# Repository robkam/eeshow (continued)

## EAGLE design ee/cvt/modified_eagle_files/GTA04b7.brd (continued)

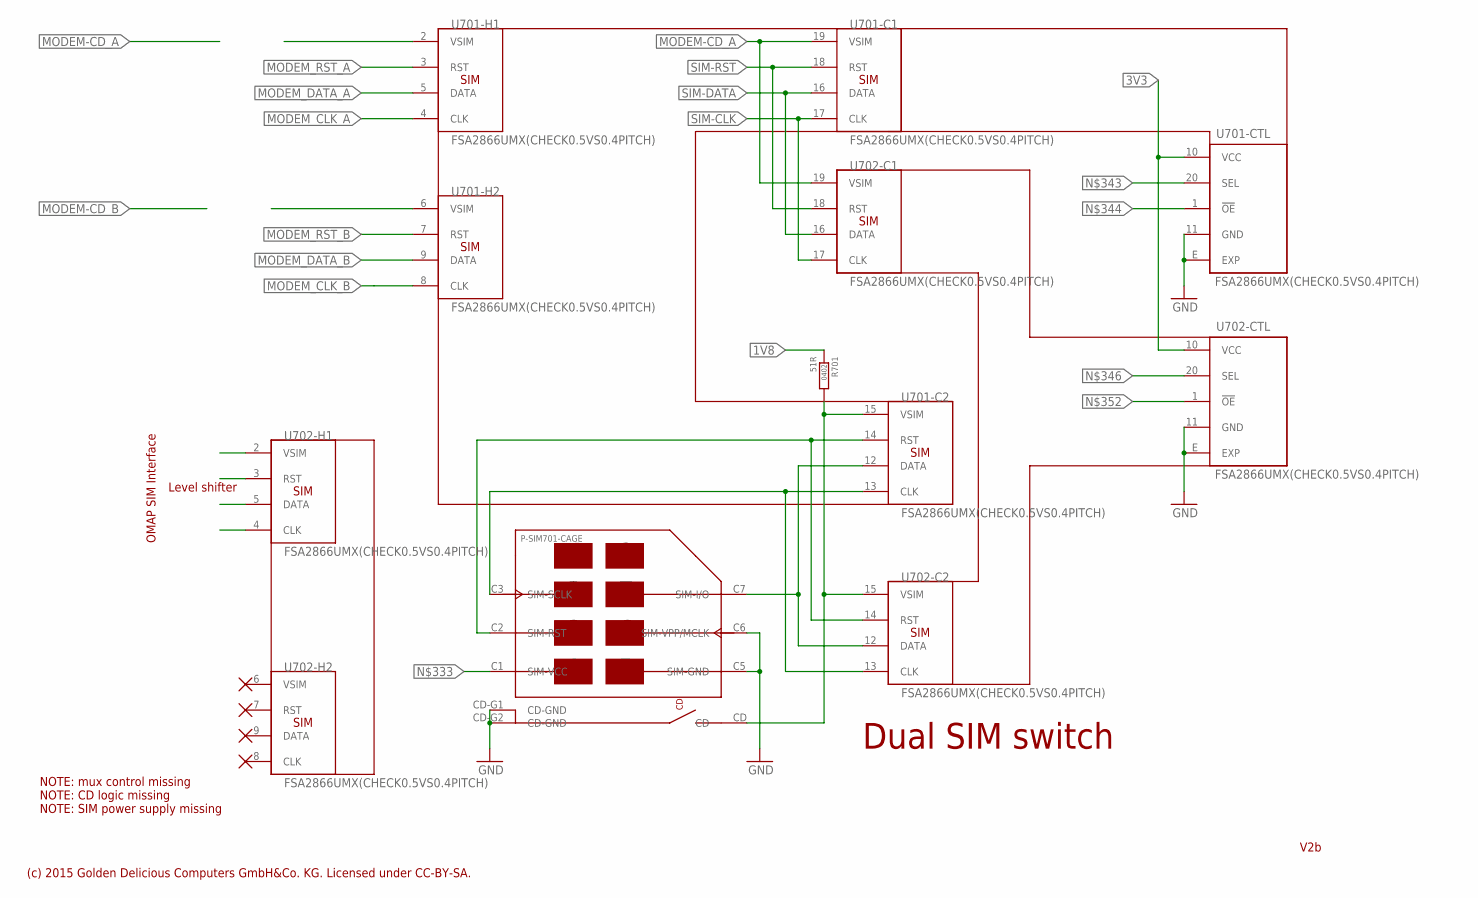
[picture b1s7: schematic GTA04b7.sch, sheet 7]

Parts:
P-SIM701: SIM-SLOT-6PIN+CD-CHECK-PINS; SJ106220
R701: 51R; SMD-0402
U701, U702: FSA2866UMX(CHECK0.5VS0.4PITCH); S-PWQFN-N20-0.5

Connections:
1V8: R701.1; also elsewhere on the board
3V3: U701.10 (VCC), U702.10 (VCC); also elsewhere on the board
GND: P-SIM701.C5 (SIM-GND), P-SIM701.C6 (SIM-VPP/MCLK), P-SIM701.CD-G1 (CD-GND), P-SIM701.CD-G2 (CD-GND), U701.11 (GND), U701.E (EXP), U702.11 (GND), U702.E (EXP); also elsewhere on the board
MODEM-CD_A: U701.19 (VSIM), U702.19 (VSIM); also elsewhere on the board
MODEM_CLK_A: U701.4 (CLK); also elsewhere on the board
MODEM_CLK_B: U701.8 (CLK)
MODEM_DATA_A: U701.5 (DATA); also elsewhere on the board
MODEM_DATA_B: U701.9 (DATA)
MODEM_RST_A: U701.3 (RST); also elsewhere on the board
MODEM_RST_B: U701.7 (RST)
unnamed: P-SIM701.C3 (SIM-SCLK), U701.13 (CLK), U702.13 (CLK)
unnamed: P-SIM701.C2 (SIM-RST), U701.14 (RST), U702.14 (RST)
unnamed: P-SIM701.CD, R701.2, U701.15 (VSIM), U702.15 (VSIM)
unnamed: P-SIM701.C7 (SIM-I/O), U701.12 (DATA), U702.12 (DATA)
SHIELD: P-SIM701.S1 (SHIELD), P-SIM701.S2 (SHIELD); also elsewhere on the board
SIM-CLK: U701.17 (CLK), U702.17 (CLK); also elsewhere on the board
SIM-DATA: U701.16 (DATA), U702.16 (DATA); also elsewhere on the board
SIM-RST: U701.18 (RST), U702.18 (RST); also elsewhere on the board
VSIM: U702.6 (VSIM)

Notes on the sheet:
Dual SIM switch
(c) 2015 Golden Delicious Computers GmbH&Co. KG. Licensed under CC-BY-SA.
V2b
Level shifter
OMAP SIM Interface
NOTE: mux control missing NOTE: CD logic missing NOTE: SIM power supply missing

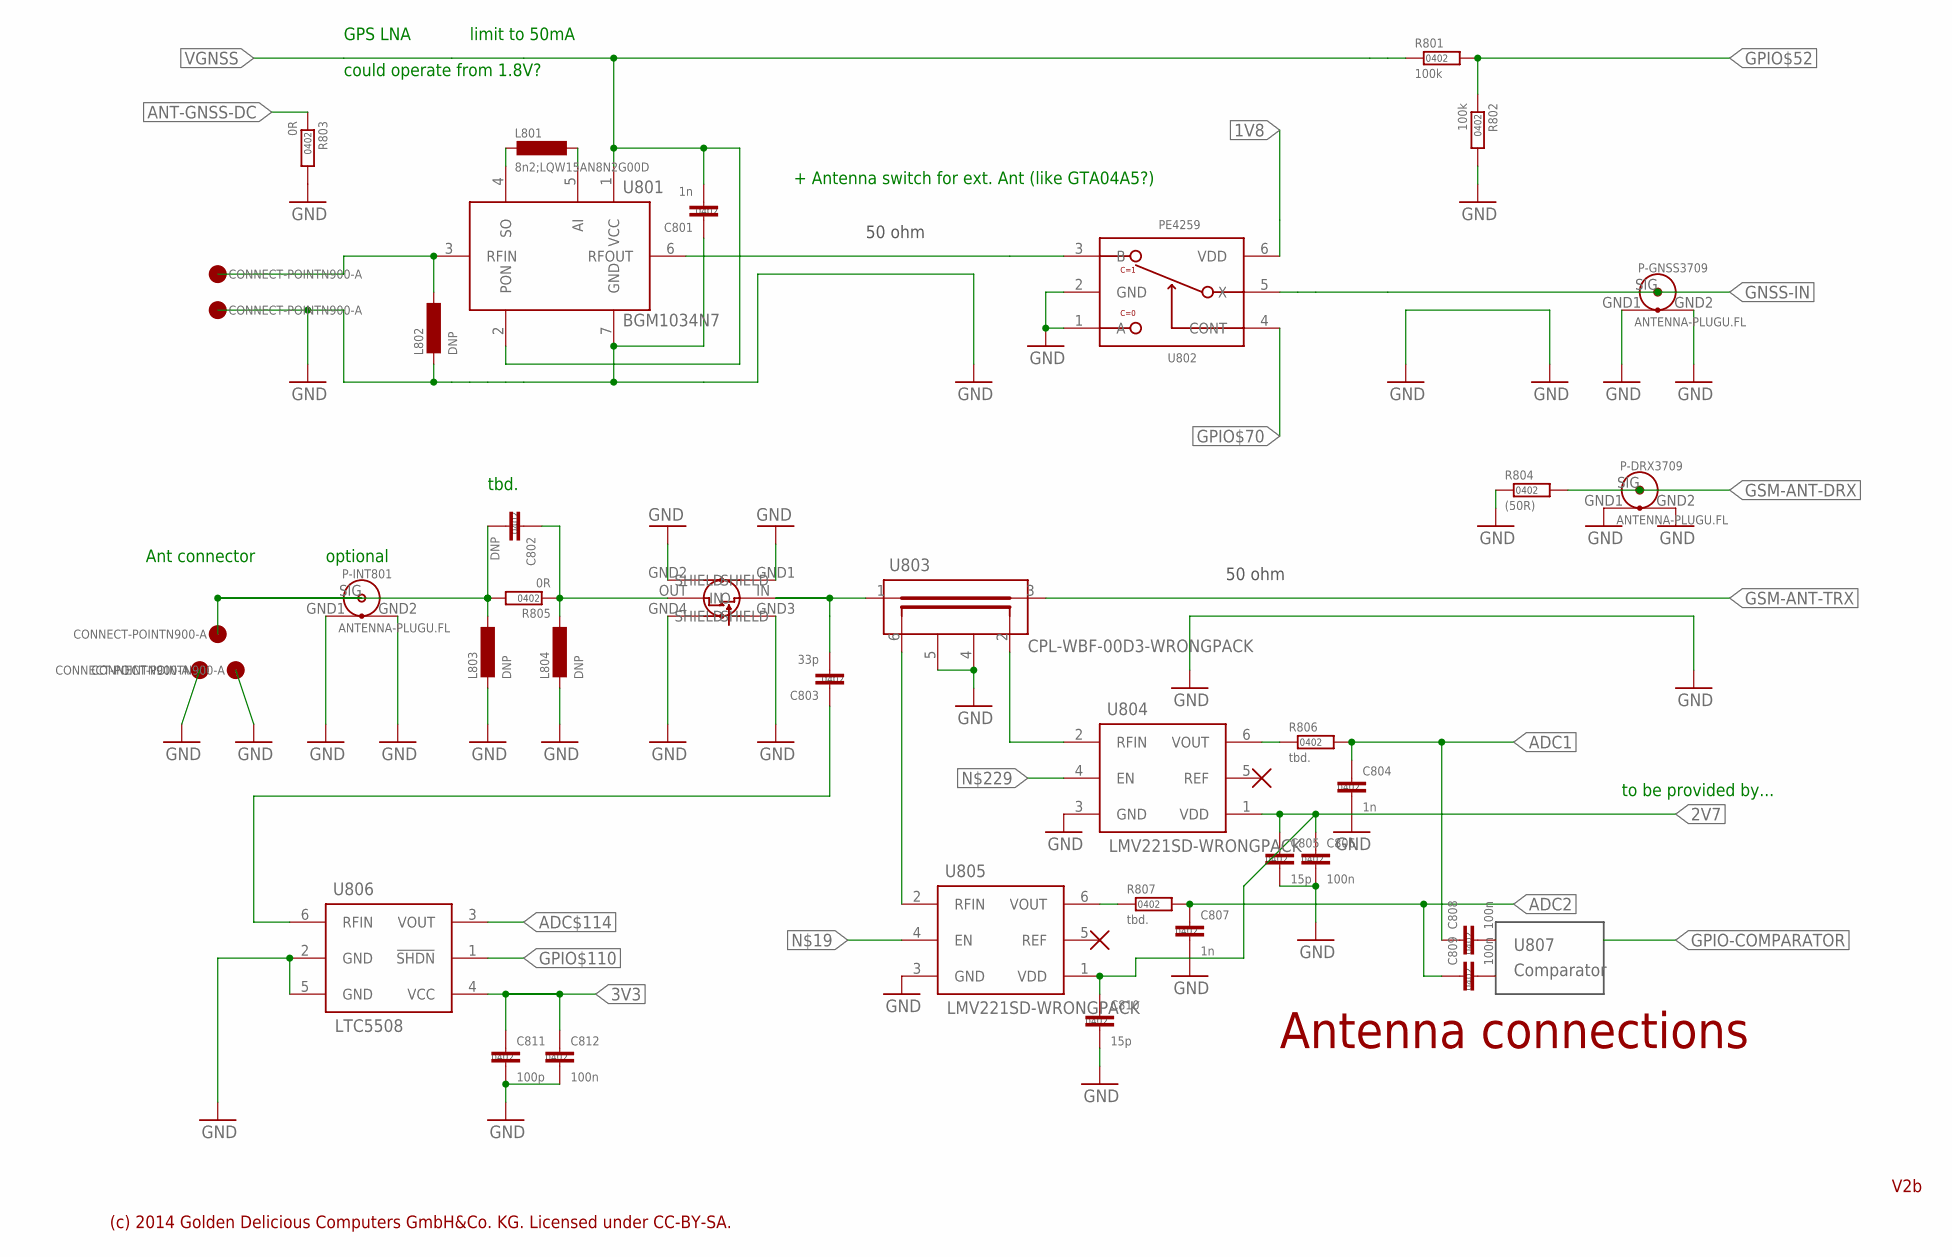
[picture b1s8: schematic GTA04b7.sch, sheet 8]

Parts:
C801, C804, C807: 1n; SMD-0402
C802: DNP; SMD-0402
C803: 33p; SMD-0402
C805, C810: 15p; SMD-0402
C806, C808, C809, C812: 100n; SMD-0402
C811: 100p; SMD-0402
GPS-ANT3709: CONNECT-POINTN900-A; N900-SPRING-A
GPS-GND3709: CONNECT-POINTN900-A; N900-SPRING-A
L801: 8n2;LQW15AN8N2G00D; SMD-0402
L802, L803, L804: DNP; SMD-0402
P-DRX3709: ANTENNA-PLUGU.FL; U.FL-SOCKET-SMT-HIROSE
P-GNSS3709: ANTENNA-PLUGU.FL; U.FL-SOCKET-SMT-HIROSE
P-INT801: ANTENNA-PLUGU.FL; U.FL-SOCKET-SMT-HIROSE
P-WWAN3709: MM8430-2600RA1; SWD-SOCKETSWITCH-SMT-MURATA
R801, R802: 100k; SMD-0402
R803, R805: 0R; SMD-0402
R804: (50R); SMD-0402
R806, R807: tbd.; SMD-0402
U801: BGM1034N7; TSNP-7-10
U802: PE4259; SC70-6
U803: CPL-WBF-00D3-WRONGPACK; SOT23-6
U804, U805: LMV221SD-WRONGPACK; SOT23-6
U806: LTC5508; SC70-6
U807: Comparator; NONE
WWAN3709: CONNECT-POINTN900-A; N900-SPRING-A
WWAN-GND801, WWAN-GND802: CONNECT-POINTN900-A; N900-SPRING-A

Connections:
1V8: U802.6 (VDD); also elsewhere on the board
2V7: C805.1, C806.1, C810.1, U804.1 (VDD), U805.1 (VDD)
3V3: C811.1, C812.1, U806.4 (VCC); also elsewhere on the board
ADC1: C804.1, C808.1, R806.2
ADC2: C807.1, C809.1, R807.2
ADC$114: U806.3 (VOUT)
ANT-GNSS: U801.6 (RFOUT), U802.3 (B)
ANT-GNSS-DC: R803.1; also elsewhere on the board
GND: C801.1, C804.2, C805.2, C806.2, C807.2, C810.2, C811.2, C812.2, GPS-GND3709.1, L802.2, L803.2, L804.2, P-DRX3709.GND1 (SHIELD), P-DRX3709.GND2 (SHIELD), P-GNSS3709.GND1 (SHIELD), P-GNSS3709.GND2 (SHIELD), P-INT801.GND1 (SHIELD), P-INT801.GND2 (SHIELD), P-WWAN3709.GND1 (SHIELD), P-WWAN3709.GND2 (SHIELD), P-WWAN3709.GND3 (SHIELD), P-WWAN3709.GND4 (SHIELD), R802.2, R803.2, R804.1, U801.7 (GND), U802.1 (A), U802.2 (GND), U803.4 (GND), U803.5 (GND), U804.3 (GND), U805.3 (GND), U806.2 (GND), U806.5 (GND), WWAN-GND801.1, WWAN-GND802.1; also elsewhere on the board
GNSS-IN: P-GNSS3709.SIG, U802.5 (X); also elsewhere on the board
GPIO$52: R801.2, R802.1
GPIO$70: U802.4 (CONT)
GPIO$110: U806.1 (!SHDN)
GSM-ANT-DRX: P-DRX3709.SIG, R804.2; also elsewhere on the board
GSM-ANT-TRX: U803.3 (OUT); also elsewhere on the board
unnamed: GPS-ANT3709.1, L802.1, U801.3 (RFIN)
unnamed: C803.2, P-WWAN3709.IN, U803.1 (IN)
unnamed: U803.6 (CPL), U805.2 (RFIN)
unnamed: C803.1, U806.6 (RFIN)
unnamed: U803.2 (ISO), U804.2 (RFIN)
unnamed: L801.2, U801.4 (SO)
unnamed: R807.1, U805.6 (VOUT)
unnamed: R806.1, U804.6 (VOUT)
unnamed: C802.2, L803.1, P-INT801.SIG, R805.2, WWAN3709.1
unnamed: C802.1, L804.1, P-WWAN3709.OUT (O), R805.1
unnamed: L801.1, U801.5 (AI)
VGNSS: C801.2, R801.1, U801.1 (VCC), U801.2 (PON); also elsewhere on the board

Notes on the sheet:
Antenna connections
(c) 2014 Golden Delicious Computers GmbH&Co. KG. Licensed under CC-BY-SA.
V2b
limit to 50mA
50 ohm
GPS LNA
could operate from 1.8V?
Ant connector
optional
tbd.
to be provided by...
+ Antenna switch for ext. Ant (like GTA04A5?)

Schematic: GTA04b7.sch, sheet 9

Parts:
1V8-OUT3709: TEST-POINT-0.75; TP-0.75
A901: 5400AT18A1000; 2450AT18A100
ANT-901: 2PIN-SOLDER-2.54MM; 2PIN2.54
C901: 1n; SMD-0402
C902, C903, C905, C906, C908: 100n; SMD-0402
C904: 4u7; SMD-0603
C907: (1n); SMD-0402
D901: V5.5MLA0603N; SMD-0603
FMTX-ANT3709: CONNECT-POINTN900-A; N900-SPRING-A
FMTX-ANT-GND3709: SHIELDPAD-3.5X2.5; PAD-3.5X2.5
L901: MLZ1608M100W; SMD-0603
L902: 120n; SMD-0402
M901: WL1837MODGIMOC; WL18XXMOD
M902: WG7351; JORJIN-WG7351
R901, R902, R903, R906: 2k2; SMD-0402
R904: 2R; SMD-0402
R905: 680R; SMD-0402
R907, R908, R910, R911: (0R); SMD-0402
R909: 0R; SMD-0402
TP1401: LOOP+; 1PIN-1.5-0.8
TP1402: LOOP-; 1PIN-1.5SQ-0.8
U901: WG7351; JORJIN-WG7351
U902: SI4721BG; QFN-16+4+E-0.5
U903: Splitter; NONE
U904: TPS22963CYZP; R-XBGA-N6-0.5
WLAN-ANT901: CONNECT-POINTN900-A; N900-SPRING-A
WLAN-ANT3709: CONNECT-POINT-POGO; POGO-TH-0965-0-15-20-80-14-11-0
WLAN-GND901: CONNECT-POINTN900-A; N900-SPRING-A
WLAN-GND3709: CONNECT-POINT-POGO; POGO-TH-0965-0-15-20-80-14-11-0
X901: NT2016SA-26.000000MHZ-NBG2; XO-2016

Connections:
1V8: C902.1, C906.1, M901.38 (VIO), M902.10 (VIO), R908.1, R909.1, U902.10 (VIO), U904.A2 (VIN), U904.B2 (VIN); also elsewhere on the board
3V3: C903.1, U902.11 (VDD); also elsewhere on the board
32KHZ: M901.36 (32KHZ), M902.26 (SLEEP_CLOCK), U902.9 (RCLK)
ANT2: M901.18 (ANT2)
BT-EN: M901.41 (BT-EN)
BT-PCM-DR: M901.57 (OUT)
BT-PCM-DX: M901.56 (IN)
FM-L-IN: M902.34 (FM_AUD_L_IN)
FM-L-OUT: M902.36 (FM_AUD_L_OUT); also elsewhere on the board
FM-R-IN: M902.33 (FM_AUD_R_IN)
FM-R-OUT: M902.35 (FM_AUD_R_OUT); also elsewhere on the board
FM-RX: C901.1, M902.30 (FM_RX_ANT); also elsewhere on the board
GND: A901.GND1 (GND), A901.GND2 (GND), ANT-901.2, C902.2, C903.2, C904.2, C905.2, C906.2, C908.2, D901.1 (A), FMTX-ANT-GND3709.1, L902.2, M901.1 (PIN), M901.7 (PIN), M901.9 (PIN), M901.15 (PIN), M901.16 (PIN), M901.17 (PIN), M901.19 (PIN), M901.20 (PIN), M901.23 (PIN), M901.24 (PIN), M901.28 (PIN), M901.29 (PIN), M901.30 (PIN), M901.31 (PIN), M901.33 (PIN), M901.34 (PIN), M901.35 (PIN), M901.37 (PIN), M901.39 (PIN), M901.44 (PIN), M901.45 (PIN), M901.48 (PIN), M901.49 (PIN), M901.54 (PIN), M901.55 (PIN), M901.59 (PIN), M901.61 (PIN), M901.63 (PIN), M901.64 (PIN), M901.G1 (PIN), M901.G2 (PIN), M901.G3 (PIN), M901.G4 (PIN), M901.G5 (PIN), M901.G6 (PIN), M901.G7 (PIN), M901.G8 (PIN), M901.G9 (PIN), M901.G10 (PIN), M901.G11 (PIN), M901.G12 (PIN), M901.G13 (PIN), M901.G14 (PIN), M901.G15 (PIN), M901.G16 (PIN), M901.G17 (PIN), M901.G18 (PIN), M901.G19 (PIN), M901.G20 (PIN), M901.G21 (PIN), M901.G22 (PIN), M901.G23 (PIN), M901.G24 (PIN), M901.G25 (PIN), M901.G26 (PIN), M901.G27 (PIN), M901.G28 (PIN), M901.G29 (PIN), M901.G30 (PIN), M901.G31 (PIN), M901.G32 (PIN), M901.G33 (PIN), M901.G34 (PIN), M901.G35 (PIN), M901.G36 (PIN), M902.1 (GND), M902.3 (GND), M902.6 (GND), M902.11 (GND), M902.18 (GND), M902.25 (GND), M902.27 (GND), M902.29 (GND), M902.31 (GND), M902.32 (GND), M902.37 (GND), M902.40 (GND), M902.46 (GND), M902.48 (GND), M902.49 (GND), M902.50 (GND), M902.59 (GND), M902.60 (GND), M902.66 (GND), M902.67 (GND), M902.68 (GND), M902.69 (GND), R907.1, TP1402.1, U901.1 (GND), U901.3 (GND), U901.6 (GND), U901.11 (GND), U901.18 (GND), U901.25 (GND), U901.27 (GND), U901.29 (GND), U901.31 (GND), U901.32 (GND), U901.37 (GND), U901.40 (GND), U901.46 (GND), U901.48 (GND), U901.49 (GND), U901.50 (GND), U901.59 (GND), U901.60 (GND), U901.66 (GND), U901.67 (GND), U901.68 (GND), U901.69 (GND), U902.3 (RFGND), U902.6 (!SEN), U902.12 (GND), U902.EXP (GND), U904.C1 (GND), WLAN-GND901.1, WLAN-GND3709.1, X901.1 (NC/GND), X901.2 (GND); also elsewhere on the board
GPIO-BT-EN: M902.12 (BT_EN)
GPIO-FM-EN: M902.14 (FM_EN)
GPIO-FMIRQ: M902.62 (FM_IRQ)
GPIO-WLAN-EN: M902.17 (WL_EN)
GPIO-WLAN-IRQ: M902.13 (WL_IRQ)
I2C2-SCL: M902.61 (FM_SCL), U902.7 (SCLK); also elsewhere on the board
I2C2-SDA: M902.63 (FM_SDA), U902.8 (SDIO); also elsewhere on the board
LOOP: D901.2 (K), R904.1, TP1401.1
MCBSP2-CLK: M902.58 (FM_I2S_CLK)
MCBSP2-DR: M902.55 (FM_I2S_DO)
MCBSP2-DX: M902.56 (FM_I2S_DI)
MCBSP2-FCK: M902.57 (FM_I2S_FSYNC)
MCBSP3-CLK: M902.52 (PCM_AUD_CLK)
MCBSP3-DR: M902.53 (PCM_AUD_OUT)
MCBSP3-DX: M902.54 (PCM_AUD_IN)
MCBSP3-FCK: M902.51 (PCM_AUD_FSYNC)
MMC3-CLK: M902.23 (SDIO_CLK)
MMC3-CMD: M902.22 (SDIO_CMD)
MMC3-DATA0: M902.24 (SDIO_D0)
MMC3-DATA1: M902.20 (SDIO_D1)
MMC3-DATA2: M902.19 (SDIO_D2)
MMC3-DATA3: M902.21 (SDIO_D3)
unnamed: M902.47 (WLAN/BT_ANT), WLAN-ANT901.1, WLAN-ANT3709.1
unnamed: R906.1, U902.16 (LIN/DFS)
unnamed: A901.ANT (SIG), M902.2 (5G-ANT)
unnamed: ANT-901.1, M902.28 (FM_TX_ANT)
unnamed: R905.1, U902.15 (RIN/DOUT)
unnamed: R901.1, U902.14 (LOUT/DFS)
unnamed: R903.1, U902.13 (ROUT/DIN)
unnamed: 1V8-OUT3709.P, M902.7 (1V8_PRE_REG)
unnamed: R902.1, U902.17 (GPO3/DCLK)
unnamed: L901.2, L902.1, U902.4 (TXO)
unnamed: L901.1, R904.2
unnamed: C901.2, U902.2 (FMI)
unnamed: M902.5 (CLK_REQ), R908.2, R910.2, U904.C2 (ON)
unnamed: C907.2, M902.38 (XTALP), R907.2
unnamed: M902.39 (XTALM), R909.2, R911.2
unnamed: C907.1, X901.3 (OUT)
unnamed: C908.1, R910.1, U904.A1 (VOUT), U904.B1 (VOUT), X901.4 (VCC)
NRESWARM: U902.5 (!RST)
SYSCLK: R911.1
UART1-CTS: M902.45 (HCI_CTS)
UART1-RTS: M902.42 (HCI_RX)
UART1-RX: M902.44 (HCI_TX)
UART1-TX: M902.43 (HCI_RTS)
VBAT: U901.9 (VBAT); also elsewhere on the board
VBATT: M901.46 (VBATT), M901.47 (VBATT)
VDD_LDO_IN_CLASS1P5: U901.8 (VDD_LDO_IN_CLASS1P5)
VIO: U901.10 (VIO)
VSYS: C904.1, C905.1, M902.8 (VDD_LDO_IN_CLASS1P5), M902.9 (VBAT); also elsewhere on the board
WLAN-EN: M901.40 (WLAN-EN)
WLAN-IRQ: M901.14 (WLAN-IRQ)

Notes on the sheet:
WLAN & Bluetooth & FM
(c) 2014 Golden Delicious Computers GmbH&Co. KG. Licensed under CC-BY-SA.
V2b
26 MHz
if we have a 26 MHz SYSCLK here
Dämpfungs-RC's?
(c) 2015 Golden Delicious Computers GmbH&Co. KG. Licensed under CC-BY-SA.
install C1101/2, L1102/4 according to antenna type
main antenna (at top of GTA04)
secondary (on the side of GTA04) could be 5.8GHz as well
Address: 0x11
Si4705 is pin compatible (mostly) but RX-only
CLKR
FSR
connect >10cm
loop or stub antenna
filter 3-4 GHz
50 Ohm???
FSX
CLKX
WiLink6
WiLink8
WiLink5

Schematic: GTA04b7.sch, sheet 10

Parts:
C1001, C1002, C1004, C1005, C1007, C1008, C1011, C1012: 100n; SMD-0402
C1003, C1006: 10u; SMD-0603
C1009: 6n8; SMD-0402
C1010: 120n; SMD-0402
R1001, R1002: (0R); SMD-0402
S1001: LIS302DLTR; LGA-DIL-12+2
S1002: BMG160
S1003: BMC150
S1004: BNO055; BNO050
S1005: BMP180

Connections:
1V8: C1005.1, C1009.1, C1010.1, C1012.1, S1001.1 (VDDIO), S1001.7 (CS), S1001.12 (SDO), S1002.6 (PS), S1002.8 (AD0), S1002.10 (VDDIO), S1003.10 (VDDIO), S1003.13 (PS), S1004.28 (VDDIO), S1005.2 (VDD), S1005.3 (VDDIO); also elsewhere on the board
3V3: C1001.1, C1002.1, C1003.1, C1004.1, C1006.1, C1007.1, C1008.1, S1001.3 (VDD), S1001.6 (VDD), S1002.2 (VDD), S1003.8 (VDD), S1004.3 (VDD); also elsewhere on the board
ACCEL-INT: R1002.2
GND: C1001.2, C1002.2, C1003.2, C1004.2, C1005.2, C1006.2, C1007.2, C1008.2, C1009.2, C1010.2, C1011.2, C1012.2, R1001.2, S1001.2 (GND), S1001.4 (GND), S1001.5 (GND), S1001.10 (GND), S1001.11 (GND), S1002.1 (GNDNC), S1002.3 (GND), S1002.11 (GNDIO), S1003.1 (SDO), S1003.6 (GND), S1003.7 (GND), S1003.9 (GND), S1004.2 (GND), S1004.5 (PS1), S1004.6 (PS0), S1004.7 (PIN7), S1004.8 (PIN8), S1004.10 (PIN10), S1004.15 (PIN15), S1004.16 (PIN16), S1004.18 (COM2), S1004.25 (GNDIO), S1005.7 (GND); also elsewhere on the board
GPIN115: S1003.2 (INT1)
GPIO56: S1002.4 (INT1)
GPIO$51: S1003.4 (DRDY)
GPIO$55: S1001.8 (INT1)
GPIO$56: S1001.9 (INT2)
I2C3-SCL: S1001.14 (SCL), S1002.7 (SCL), S1003.11 (SCK), S1004.19 (COM1/SCL), S1005.5 (SCL); also elsewhere on the board
I2C3-SDA: S1001.13 (SDI), S1002.9 (SDA), S1003.14 (SDI), S1004.20 (COM0/SDA), S1005.6 (SDA); also elsewhere on the board
unnamed: C1011.1, S1004.9 (CAP)
unnamed: R1001.1, S1004.11 (RESET)
unnamed: R1002.1, S1004.14 (INT)

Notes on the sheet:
Sensors
Addr: 0x77
(c) 2014 Golden Delicious Computers GmbH&Co. KG. Licensed under CC-BY-SA.
Addr: 0x69
Addr: 0x12
Addr: 0x18
keep away from magnets and metal
keep away from temperatures
Addr: 0x1d
V2b
Addr: 0x28/9

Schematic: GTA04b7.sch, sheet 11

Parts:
C1101, C1106, C1109, C1110, C1111: 3n3; SMD-0402
C1102, C1104, C1107: 2u2; SMD-0402
C1103, C1105, C1108: 100n; SMD-0402
L1101: tdb.; MPZ1608
L1102, L1103: tbd.; MPZ1608
R1101: 100; SMD-0402
R1102, R1103, R1104, R1105, R1106, R1107, R1108, R1109, R1110, R1111: 560; SMD-0402
U1101: tlv320aic34; S-PBGA-N87-0.5

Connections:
1V8: L1103.2; also elsewhere on the board
DMIC-BIAS: U1101.B10 (MICBIAS)
DMIC-CLOCK: R1101.1
DMIC-DATA: U1101.H2 (GPIO2)
EAR+: U1101.A8
EAR-: U1101.A7 (N)
FM-L-OUT: U1101.H10; also elsewhere on the board
FM-R-OUT: U1101.F10; also elsewhere on the board
GND: C1102.2, C1103.2, C1104.2, C1105.2, C1107.2, C1108.2, U1101.D4 (AVSS_DAC), U1101.D5 (DRVSS), U1101.D6 (DRVSS), U1101.D7 (DRVSS), U1101.D8 (AVSS_ADC), U1101.E4 (AVSS_DAC), U1101.E8 (DVSS), U1101.F4 (AVSS_DAC), U1101.F8 (DVSS), U1101.G4 (AVSS_DAC), U1101.G8 (DVSS), U1101.H4 (DVSS), U1101.H5 (DVSS), U1101.H6 (DVSS), U1101.H8 (DVSS); also elsewhere on the board
HFL+: C1110.1, R1106.2; also elsewhere on the board
HFL-: C1110.2, R1107.2; also elsewhere on the board
HFR+: C1111.1, R1108.2; also elsewhere on the board
HFR-: C1111.2, R1109.2; also elsewhere on the board
HSL+: C1106.1, R1102.2; also elsewhere on the board
HSL-: C1106.2, R1103.2; also elsewhere on the board
HSR+: C1109.1, R1104.2; also elsewhere on the board
HSR-: C1109.2, R1105.2; also elsewhere on the board
I2C2-SCL: U1101.L9 (SCL); also elsewhere on the board
I2C2-SDA: U1101.L6 (SDA); also elsewhere on the board
MIC+: U1101.K9; also elsewhere on the board
MIC-: U1101.L10 (N); also elsewhere on the board
MICBIAS: U1101.B11 (MICBIAS)
unnamed: U1101.G1 (!RESETB), U1101.G2 (!RESETB)
unnamed: C1107.1, C1108.1, L1103.1, U1101.H7 (IOVDD), U1101.K1 (DVDD), U1101.K7 (IOVDD)
unnamed: C1104.1, C1105.1, L1102.1, U1101.A4 (DRVDD), U1101.A9 (DRVDD), U1101.B4 (DRVDD), U1101.B9 (DRVDD)
unnamed: R1101.2, U1101.J2 (GPIO1)
unnamed: R1102.1, U1101.B8
unnamed: R1103.1, U1101.B7 (N)
unnamed: R1106.1, U1101.C2
unnamed: R1107.1, U1101.D2 (N)
unnamed: R1110.1, U1101.A3
unnamed: C1101.1, R1110.2, U1101.E11 (N)
unnamed: R1105.1, U1101.B6 (N)
unnamed: R1104.1, U1101.B5
unnamed: R1108.1, U1101.E2
unnamed: R1109.1, U1101.F2 (N)
unnamed: C1101.2, R1111.2, U1101.F11
unnamed: R1111.1, U1101.A2 (N)
unnamed: C1102.1, C1103.1, L1101.1, U1101.B3 (AVDD_DAC)
VMMC2: L1101.2, L1102.2; also elsewhere on the board

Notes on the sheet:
Audio Codec
(c) 2014 Golden Delicious Computers GmbH&Co. KG. Licensed under CC-BY-SA.
problem: analog mic is on upper board!
problem: this is a 0.5mm BGA making lower board expensive!
alternative: place on upper board (to be evaluated)
but it appears to be not extremely critical (only 3 rows and inner ring is GND)
address: 0x18-0x1b
conflict with bmc150?
mcbsp1
Channel A+B
V2b

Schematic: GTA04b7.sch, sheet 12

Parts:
C1201, C1202, C1203, C1210: 1u; SMD-0402
C1204, C1206, C1207, C1209: 470n; SMD-0402
C1205, C1208: 22p; SMD-0402
C1211, C1217: 100n; SMD-0402
C1212: 2u2; SMD-0402
C1213, C1214: 33n; SMD-0402
C1215, C1216: 1n; SMD-0402
D1201, D1202, D1203, D1204, D1205: V5.5MLA0603N; SMD-0603
HS-1201, HS-1202, HS-1203, HS-1204, HS-1205, HS-1206: TEST-POINT-1.25; TP-1.25
L1201, L1207: MPZ1608S221A; MPZ1608
L1202, L1203, L1204, L1205, L1206: tbd; SMD-0402
P-HS3709: N900-HEADSET
R1201: 470k; SMD-0402
R1202: 100k; SMD-0402
R1203, R1208: 10k; SMD-0402
R1204: 220R; SMD-0402
R1205: 2k; SMD-0402
R1206, R1207: 2k2; SMD-0402
U1201: TS5A22366; NONE
U1202: TPA6130A2RTJ; S-PWQFN-N20-0.5
U1203: TS3A225ERTE; S-PWQFN-N16-0.5

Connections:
1V8: R1202.2; also elsewhere on the board
AGND: C1201.2, C1202.1, C1210.1, C1211.1, C1215.2, C1216.2, C1217.1, D1201.2 (K), D1202.2 (K), D1203.1 (A), D1204.1 (A), D1205.1 (A), L1207.1, R1208.1, U1202.3 (AGND), U1202.9 (GND), U1202.10 (GND), U1202.13 (GND), U1202.19 (CPGND), U1202.E (PAD), U1203.3 (GND), U1203.4 (ADDR_SEL), U1203.10 (GND), U1203.E (PAD)
FM-RX: C1205.1, C1208.1; also elsewhere on the board
GND: C1212.2, L1207.2; also elsewhere on the board
GPIO177: R1202.1, R1203.2
GPIO$60: U1203.8 (!MIC_PRESENT)
GPIO-HP-EN: U1202.6 (!SD)
HSL+: C1204.2; also elsewhere on the board
HSL-: C1206.2; also elsewhere on the board
HSR+: C1207.2; also elsewhere on the board
HSR-: C1209.2; also elsewhere on the board
I2C2-SCL: U1202.8 (SCL), U1203.1 (SCL); also elsewhere on the board
I2C2-SDA: U1202.7 (SDA), U1203.2 (SDA); also elsewhere on the board
MIC+: C1213.2; also elsewhere on the board
MIC-: C1214.2; also elsewhere on the board
MIC-BIAS: R1204.1
MIC-ECI: R1205.2, R1206.2, U1203.11 (MIC+); also elsewhere on the board
unnamed: C1210.2, U1202.15 (CPVSS), U1202.16 (CPVSS)
unnamed: C1203.2, U1202.18 (CP+)
unnamed: C1203.1, U1202.17 (CP-)
unnamed: C1204.1, U1202.2 (L-IN+)
unnamed: C1206.1, U1202.1 (L-IN-)
unnamed: C1207.1, U1202.4 (R-IN+)
unnamed: C1209.1, U1202.5 (R-IN-)
unnamed: R1207.2, U1203.12 (MIC-)
unnamed: C1213.1, C1215.1, R1206.1
unnamed: C1214.1, C1216.1, R1207.1
unnamed: D1203.2 (K), L1202.2, U1203.6 (SLEEVE), U1203.15 (SLEEVE_SENSE)
unnamed: D1205.2 (K), L1206.2, U1203.7 (RING2), U1203.14 (RING2_SENSE)
unnamed: D1201.1 (A), L1203.2, U1202.11 (R-OUT)
unnamed: C1217.2, D1202.1 (A), L1204.2, R1201.2, R1203.1, U1203.5 (DET_TRIGGER)
unnamed: D1204.2 (K), L1205.2, R1208.2, U1202.14 (L-OUT), U1203.9 (TIP_SENSE)
unnamed: C1201.1, C1202.2, L1201.1, U1202.12 (AVDD), U1202.20 (CPVDD)
unnamed: C1212.1, R1204.2, R1205.1
unnamed: HS-1201.P, HS-1202.P, L1202.1, P-HS3709.2 (SH), P-HS3709.6 (4GND)
unnamed: HS-1204.P, L1204.1, P-HS3709.4 (SW)
unnamed: C1205.2, HS-1205.P, L1205.1, P-HS3709.3 (1L)
unnamed: HS-1206.P, L1206.1, P-HS3709.5 (3M)
unnamed: C1208.2, HS-1203.P, L1203.1, P-HS3709.1 (2R)
VMMC2: C1211.2, L1201.2, R1201.1, U1203.13 (VDD), U1203.16 (VDD); also elsewhere on the board

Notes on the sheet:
Audio Headset & Mic
(c) 2014 Golden Delicious Computers GmbH&Co. KG. Licensed under CC-BY-SA.
address: 0x3b
address: 0x60
Head Set
Microphone Switch
Video Switch
V2b
do not install R301 and R45!

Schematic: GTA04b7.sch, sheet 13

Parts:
R1301, R1310: 6k8; SMD-0402
R1302, R1308, R1309: 22k; SMD-0402
R1303: 32k; SMD-0402
R1304, R1305: 47k; SMD-0402
R1306: 470R; SMD-0402
R1307, R1311: 1k; SMD-0402
U1301: TLV702225DBV; SOT23-5
U1302: TLV1702DGK; R-PDSO-G8-0.65

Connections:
1V8: R1304.2, R1305.2, U1301.3 (EN); also elsewhere on the board
2V5: R1301.2, R1302.2, U1301.5 (OUT), U1302.8 (VDD)
3V3: U1301.1 (IN); also elsewhere on the board
ECI-ADC: R1311.1
GND: R1309.1, R1310.1, U1301.2 (GND), U1302.4 (VSS); also elsewhere on the board
GPIO-ECI0: R1305.1, R1308.2, U1302.7 (2O)
GPIO-ECI1: R1303.2, R1304.1, U1302.1 (1O)
MIC-ECI: R1306.1, R1307.1, R1311.2; also elsewhere on the board
unnamed: R1302.1, R1310.2, U1302.6 (2-)
unnamed: R1301.1, R1309.2, U1302.2 (1-)
unnamed: R1303.1, R1306.2, U1302.3 (1+)
unnamed: R1307.2, R1308.1, U1302.5 (2+)

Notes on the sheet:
ECI
(c) 2014 Golden Delicious Computers GmbH&Co. KG. Licensed under CC-BY-SA.
V2b
video switch missing!

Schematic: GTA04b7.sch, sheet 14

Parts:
C1401: 10u; SMD-0603
C1402, C1406, C1407, C1408, C1409: 100n; SMD-0402
C1403: 27p; SMD-0402
C1404, C1405, C1410, C1411: 1n; SMD-0402
D1401, D1402, D1403, D1404: V5.5MLA0603N; SMD-0603
L1401, L1402, L1403, L1404: L0402; SMD-0402
SPKR-L3709: SPEAKER; 2403-260-00031
SPKR-R3709: SPEAKER; 2403-260-00031
SPKRL+3709: TEST-POINT-1.25; TP-1.25
SPKRL-3709: TEST-POINT-1.25; TP-1.25
SPKRR+3709: TEST-POINT-1.25; TP-1.25
SPKRR-3709: TEST-POINT-1.25; TP-1.25
U1401: TPA2012D2RTJ; S-PWQFN-N20-0.5

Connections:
GND: C1401.1, C1402.1, C1403.1, C1404.1, C1405.1, C1410.2, C1411.2, D1401.2 (K), D1402.2 (K), D1403.1 (A), D1404.1 (A), U1401.1 (G1), U1401.4 (PGND), U1401.12 (PGND), U1401.15 (G0), U1401.18 (AGND), U1401.E (PAD); also elsewhere on the board
GPIO-HF-EN: U1401.7 (!SDL), U1401.8 (!SDR)
HFL+: C1406.2; also elsewhere on the board
HFL-: C1407.2; also elsewhere on the board
HFR+: C1408.2; also elsewhere on the board
HFR-: C1409.2; also elsewhere on the board
unnamed: C1404.2, D1402.1 (A), L1402.1, SPKR-L3709.- (N), SPKRL-3709.P
unnamed: C1410.1, D1403.2 (K), L1404.1, SPKR-R3709.- (N), SPKRR-3709.P
unnamed: C1405.2, D1401.1 (A), L1401.1, SPKR-L3709.+, SPKRL+3709.P
unnamed: C1406.1, U1401.19 (IN-)
unnamed: C1407.1, U1401.20 (IN+)
unnamed: C1408.1, U1401.17 (IN-)
unnamed: C1409.1, U1401.16 (IN+)
unnamed: L1401.2, U1401.5 (OUT-)
unnamed: L1402.2, U1401.2 (OUT+)
unnamed: L1403.2, U1401.11 (OUT-)
unnamed: L1404.2, U1401.14 (OUT+)
SPKRR+: C1411.1, D1404.2 (K), L1403.1, SPKR-R3709.+, SPKRR+3709.P
VSYS: C1401.2, C1402.2, C1403.2, U1401.3 (PVDD), U1401.9 (AVDD), U1401.13 (PVDD); also elsewhere on the board

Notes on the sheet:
Audio Handsfree
(c) 2014 Golden Delicious Computers GmbH&Co. KG. Licensed under CC-BY-SA.
Hands Free
V2b

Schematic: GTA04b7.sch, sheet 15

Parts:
G1501, G1502, G1503: SHIELDPAD-3.5X2.5; PAD-3.5X2.5
P1501: FX6-20-PLUG; FX6-20S-0.8SV
VIBRA3709: PREC-MICRO-304-106
VIBRA+3709: TEST-POINT-1.25; TP-1.25
VIBRA-3709: TEST-POINT-1.25; TP-1.25

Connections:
3V3: P1501.15; also elsewhere on the board
GND: G1501.1, G1502.1, G1503.1, P1501.1, P1501.12, P1501.19, VIBRA3709.SHIELD; also elsewhere on the board
GPIO-BATT-LID: P1501.17
GPIO-CAM-COVER: P1501.13
GPIO-FLASH-EN: P1501.9
GPIO-FLASH-INT: P1501.11
GPIO-FLASH-STR: P1501.7
I2C2-SCL: P1501.5; also elsewhere on the board
I2C2-SDA: P1501.3; also elsewhere on the board
SD-CD: P1501.20
SD-CLK: P1501.10
SD-CMD: P1501.6
SD-DAT0: P1501.16
SD-DAT1: P1501.14
SD-DAT2: P1501.2
SD-DAT3: P1501.4
SD-VDD: P1501.8
VIB+: VIBRA3709.2, VIBRA+3709.P
VIB-: VIBRA3709.1 (N), VIBRA-3709.P
VSYS: P1501.18; also elsewhere on the board

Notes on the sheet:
Misc (lower)
(c) 2014 Golden Delicious Computers GmbH&Co. KG. Licensed under CC-BY-SA.
to uSD breakout
FX6-20P-0.8SV
V2b
P1201
Vibramotor
Shield

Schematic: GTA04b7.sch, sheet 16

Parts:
C1601, C1603, C1618, C1622, C1624, C1627: 2u2; SMD-0402
C1602, C1604, C1610, C1619, C1623, C1628: 10n; SMD-0402
C1605, C1608: 10p; SMD-0402
C1606: 47p; SMD-0402
C1607, C1609: 1n5; SMD-0402
C1611, C1620: 1n2; SMD-0402
C1612, C1621: 680p; SMD-0402
C1613, C1617: DNP; SMD-0402
C1614: 220p; SMD-0402
C1615: 100p; SMD-0402
C1616, C1625, C1626: 27p; SMD-0402
L1601: 150n; SMD-0603
L1602: 330n; SMD-0603
R1601: 1k; SMD-0402
U1601: TRF7970A; TRF7960_61
X1601: 13.56MHz; XO-3225

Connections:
1V8: C1601.1, C1602.1, U1601.16 (VDD_I/O); also elsewhere on the board
3V3: C1619.1, C1622.1, U1601.2 (VIN); also elsewhere on the board
GND: C1601.2, C1602.2, C1603.1, C1604.1, C1610.2, C1612.2, C1613.2, C1615.2, C1616.2, C1617.2, C1618.2, C1619.2, C1620.2, C1621.2, C1622.2, C1623.2, C1624.2, C1625.2, C1626.2, C1627.2, C1628.2, R1601.1, U1601.6 (VSS_PA), U1601.7 (VSS_RX), U1601.10 (VSS), U1601.15 (VSS_A), U1601.17 (I/0_0), U1601.25 (EN2), U1601.29 (VSS_D), U1601.TP (THERMAL), X1601.2, X1601.4; also elsewhere on the board
unnamed: C1603.2, C1604.2, U1601.11 (BAND_GAP)
unnamed: C1607.1, C1609.1, U1601.5 (TX_OUT)
unnamed: C1607.2, C1609.2, L1601.2
unnamed: C1605.1, C1611.1, C1612.1, C1613.1, L1601.1, L1602.2
unnamed: C1611.2, C1620.1, U1601.8 (RX_IN1)
unnamed: C1605.2, C1606.1, C1608.1, C1614.1, C1615.1, C1616.1, L1602.1
unnamed: C1614.2, C1621.1, U1601.9 (RX_IN2)
unnamed: C1610.1, C1618.1, U1601.3 (VDD_RF), U1601.4 (VDD_PA)
unnamed: C1623.1, C1624.1, U1601.1 (VDD_A)
unnamed: C1625.1, U1601.30 (OSC_OUT), X1601.1
unnamed: C1626.1, U1601.31 (OSC_IN), X1601.3 (2)
unnamed: C1627.1, C1628.1, U1601.32 (VDD_X)
NFC-ANT: C1606.2, C1608.2, C1617.1, R1601.2; also elsewhere on the board
NFC-ASKOOK: U1601.12 (ASK/OOK); also elsewhere on the board
NFC-CLK: U1601.27 (SYS_CLK); also elsewhere on the board
NFC-EN: U1601.28 (EN); also elsewhere on the board
NFC-IO1: U1601.18 (I/O_1); also elsewhere on the board
NFC-IRQ: U1601.13 (IRQ); also elsewhere on the board
NFC-MISO: U1601.23 (I/O_6); also elsewhere on the board
NFC-MOSI: U1601.24 (I/O_7); also elsewhere on the board
NFC-SCLK: U1601.26 (DATA_CLK); also elsewhere on the board
NFC-SS: U1601.21 (I/O_4); also elsewhere on the board
NFC-TRXCLK: U1601.22 (I/O_5); also elsewhere on the board
NFC-TXD/MOD: U1601.14 (MOD), U1601.20 (I/O_3)
NFC-TXEN: U1601.19 (I/O_2); also elsewhere on the board

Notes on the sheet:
2.7 - 5.5V
1.8 - VIN
RFID/NFC Reader
(c) 2015 Golden Delicious Computers GmbH&Co. KG. Licensed under CC-BY-SA.
V2b
27 MHz?

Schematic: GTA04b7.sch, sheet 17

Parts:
C1701: (47pF); SMD-0402
C1702: 100n; SMD-0402
C1703: 1u; SMD-0402
D1701: LED-0603; SMD-0603D
R1701, R1702: 150R; SMD-0402
R1703, R1704: (0R); SMD-0402
U1701: MKL16Z128VFM4; QFN-32+E-0.5

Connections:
1V8: C1702.1, C1703.1, U1701.7 (PIN), U1701.15 (PIN); also elsewhere on the board
?-SCL: U1701.20 (PTB0/LLWU_P5)
?-SDA: U1701.21 (PTB1)
GND: C1701.2, C1702.2, C1703.2, U1701.8 (PIN), U1701.16 (PIN), U1701.EXP (PIN); also elsewhere on the board
unnamed: D1701.K, U1701.24 (PTC3/LLWU_P7)
unnamed: R1703.2, U1701.26 (PTC5/LLWU_P9)
unnamed: R1701.1, U1701.32 (PTD7)
unnamed: C1701.1, U1701.9 (PTE30)
unnamed: R1704.2, U1701.22 (PTC1/LLWU_P6/RTC_CLKIN)
unnamed: R1702.1, U1701.31 (PTD6/LLWU_P15)
NFC-ASKOOK: U1701.13 (PTA3); also elsewhere on the board
NFC-CLK: U1701.17 (PTA18); also elsewhere on the board
NFC-EN: U1701.12 (PTA2); also elsewhere on the board
NFC-IO1: U1701.18 (PTA19); also elsewhere on the board
NFC-IRQ: U1701.11 (PTA1); also elsewhere on the board
NFC-MISO: R1703.1, U1701.1 (PTE0), U1701.6 (PTE19); also elsewhere on the board
NFC-MOD: R1704.1, U1701.2 (PTE1)
NFC-MOSI: U1701.5 (PTE18); also elsewhere on the board
NFC-SCLK: U1701.4 (PTE17); also elsewhere on the board
NFC-SS: U1701.3 (PTE16); also elsewhere on the board
NFC-TRXCLK: U1701.30 (PTD5); also elsewhere on the board
NFC-TXEN: U1701.10 (PTA0); also elsewhere on the board
OMAP_NFC_INT: U1701.23 (PTC2)
OMAP_~NFC_RESET: U1701.19 (PTA20)
SELF: U1701.25 (PTC4/LLWU_P8), U1701.29 (PTD4/LLWU_P14)
SWIO-A: R1701.2, U1701.28 (PTC7)
SWIO-B: R1702.2, U1701.27 (PTC6/LLWU_P10)

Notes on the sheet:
RFID/NFC Controller
(c) 2015 Golden Delicious Computers GmbH&Co. KG. Licensed under CC-BY-SA.
V2b
to OMAP or I/O-expander

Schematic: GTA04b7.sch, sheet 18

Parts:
TP1, TP3, TP4, TP5: GND; 1PIN-1.5-0.8
TP6: UART_CTS; 1PIN-1.5-0.8
TP7: UART_TX; 1PIN-1.5-0.8
TP8: GPIO_b; 1PIN-1.5-0.8
TP9: GPIO_d; 1PIN-1.5-0.8
TP10: GPIO_f/3V3; 1PIN-1.5-0.8
TP11: VBUS; 1PIN-1.5-0.8
TP12, TP19: VBAT; 1PIN-1.5-0.8
TP13: UART_RTS; 1PIN-1.5-0.8
TP14: UART_RX; 1PIN-1.5-0.8
TP15: GPIO_a; 1PIN-1.5-0.8
TP16: GPIO_c; 1PIN-1.5-0.8
TP17: GPIO_e; 1PIN-1.5-0.8
TP18: VSYS; 1PIN-1.5-0.8
TP20: USB_DP; 1PIN-1.5-0.8
TP21: USB_GND; 1PIN-1.5-0.8
TP22: USB_DM; 1PIN-1.5-0.8
TP25: NFC_GND; 1PIN-1.5-0.8
TP26: NFC_ANT; 1PIN-1.5-0.8

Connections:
BATT: TP12.1, TP19.1; also elsewhere on the board
GND: TP1.1, TP3.1, TP4.1, TP5.1, TP21.1, TP25.1; also elsewhere on the board
NFC-ANT: TP26.1; also elsewhere on the board
UART3_CTS: TP6.1
UART3_RTS: TP13.1
UART3_RX: TP14.1
UART3_TX: TP7.1
USB-WWAN-D+: TP20.1; also elsewhere on the board
USB-WWAN-D-: TP22.1; also elsewhere on the board
VBUS: TP11.1; also elsewhere on the board
VSYS: TP18.1; also elsewhere on the board

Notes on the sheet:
Hackerbus
(c) 2015 Golden Delicious Computers GmbH&Co. KG. Licensed under CC-BY-SA.
V2b
NOTE: this is mangling up Breakout and Lower board connectors Signals may have to be fed through the breakout board connector increasing resistance
Missing 10 level shifter chip (or do we really have the space for 10x discrete T+R+D ca. 3x3mm each?)
Missing 6x 2R for alternate function select (do we have the space for ca. 2.5 x 5mm?)

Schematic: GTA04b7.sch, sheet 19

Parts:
C1901: 1n; SMD-0402
C1902: 100n; SMD-0402
C1903, C1904: 100p; SMD-0402
D1901: VEMD10940F; VSMB2948SL
D1902: VSMB2948SL
R1901: 4M7; SMD-0402
R1902: 10M; SMD-0402
R1903: 50k; SMD-0402
R1904: 33k; SMD-0402
R1905: 10k; SMD-0402
R1906: 1M5; SMD-0402
R1907: 1R5; SMD-0402
R1908: 22k; SMD-0402
T1901: T-PMOS-FDY100PZ; SC89-3
T1902: UMG5N; SC88A
U1901: TLV7256ISSOP; PW_R-PDSO-G08
U1902: RPM973-H11E2A

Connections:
1V8: D1901.K, R1901.2, U1902.6 (VIO); also elsewhere on the board
3V3: U1902.5 (VCC); also elsewhere on the board
AUDIOIN: C1901.2
BQ.GPIO: T1901.1 (P$GATE), U1902.4 (PWRDN); also elsewhere on the board
GND: C1902.2, R1906.1, R1908.1, T1902.2 (GND), U1902.7 (GND); also elsewhere on the board
unnamed: D1902.K, T1902.4 (C2), T1902.5 (C1)
unnamed: C1903.2, T1902.1 (B1)
unnamed: D1902.A, R1907.1
unnamed: C1902.1, R1901.1, R1903.2, R1904.1, R1906.2
unnamed: C1901.1, D1901.A, R1903.1, T1901.2 (P$SOURCE)
unnamed: C1904.2, T1902.3 (B2)
unnamed: R1902.2, R1905.1, U1901.1 (1O), U1902.3 (RXD)
unnamed: R1908.2, T1901.3 (P$DRAIN), U1901.2 (1-)
unnamed: R1902.1, R1904.2, U1901.3 (1+)
SHIELD: U1902.S (SHIELD); also elsewhere on the board
UART3-CTS_RCTX: C1904.1
UART3-RX_IRRX: R1905.2
UART3-TX_IRTX: C1903.1, U1902.2 (TXD)
VDD: U1901.8 (VDD)
VSS: U1901.4 (VSS); also elsewhere on the board
VSYS: R1907.2, U1902.1 (LEDA); also elsewhere on the board

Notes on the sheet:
Infrared
(c) 2015 Golden Delicious Computers GmbH&Co. KG. Licensed under CC-BY-SA.
V2b
alternative?
BQ.GPIO: which voltage level?
fix footprint!
NOTE: 1V8 may be quite noisy!
replace by NCX2200
Choose the right type, polarity, gain etc.

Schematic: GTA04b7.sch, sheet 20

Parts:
P2001, P2002: DF40C-60DS-0.4V

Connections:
GND: P2001.2, P2001.29, P2001.32, P2001.59, P2002.2, P2002.29, P2002.32, P2002.59; also elsewhere on the board
VSYS: P2001.1, P2001.30, P2001.31, P2001.60, P2002.1, P2002.30, P2002.31, P2002.60; also elsewhere on the board

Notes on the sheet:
B2B to upper board
(c) 2014 Golden Delicious Computers GmbH&Co. KG. Licensed under CC-BY-SA.
V2b
Pin assignment musr be optimized for final component placement
we might have to switch to 80 or 100 pin connectors
ca. 130 signals (to be counted exactly after definition of upper/lower split)

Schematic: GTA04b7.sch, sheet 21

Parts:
C2101: 1u; SMD-0402
C2102: 47n; SMD-0402
C2103: 100n; SMD-0603
C2104: 4u7; 12V; SMD-0603
C2105: 10u; SMD-0603
CD3709: TEST-POINT-1.25; TP-1.25
D2101: V5.5MLA0603N; SMD-0603
D2102: RSX101M-30; CRS02
L2101: ferrite; SMD-0805
L2102: 2u2; SMD-0805
LED2101, LED2103: CLN6A-MKW-CJ0K0233; CLN6A
LED2102: LED-0603; SMD-0603D
P2101: FX6-20; FX6-20P-0.8SV
P-MICRO-SD3709: ST1W008S4BR1500
R2101: tbd.; SMD-0402
U2101: MLX90248ESE; SOT23
U2102: SFH7741
U2103: ADP1653; QFN-16+E-0.5

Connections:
GND2: C2101.2, C2102.2, C2103.2, C2104.2, C2105.2, D2101.1 (A), P2101.1, P2101.12, P2101.19, P-MICRO-SD3709.6 (SD-VSS), P-MICRO-SD3709.S1 (GND), P-MICRO-SD3709.S2 (GND), P-MICRO-SD3709.S3 (GND), P-MICRO-SD3709.S4 (GND), R2101.2, U2101.3 (GND), U2102.2 (GND), U2102.4 (TEST), U2103.8 (GND), U2103.10 (INTF), U2103.12 (GND), U2103.EXP (GND)
LID: P2101.17, U2101.2 (OUT)
unnamed: P2101.13, U2102.3 (OUT)
unnamed: CD3709.P, D2101.2 (K), P2101.20, P-MICRO-SD3709.SW (CD)
unnamed: P2101.2, P-MICRO-SD3709.1 (SD-DAT2)
unnamed: P2101.4, P-MICRO-SD3709.2 (SD-DAT3/CD)
unnamed: P2101.6, P-MICRO-SD3709.3 (SD-CMD)
unnamed: C2103.1, P2101.8, P-MICRO-SD3709.4 (SD-VDD)
unnamed: P2101.10, P-MICRO-SD3709.5 (SD-CLK)
unnamed: P2101.14, P-MICRO-SD3709.7 (SD-DAT0)
unnamed: P2101.16, P-MICRO-SD3709.8 (SD-DAT1)
unnamed: LED2101.1 (K), LED2101.2 (K), LED2101.3 (K), LED2101.HS, LED2103.4 (A), LED2103.5 (A), LED2103.6 (A)
unnamed: D2102.A, L2102.1, U2103.13 (LX)
unnamed: R2101.1, U2102.6 (PROG)
unnamed: C2104.1, D2102.K, LED2101.4 (A), LED2101.5 (A), LED2101.6 (A), U2103.7 (OUT)
unnamed: LED2102.K, U2103.6 (ILED)
unnamed: LED2103.1 (K), LED2103.2 (K), LED2103.3 (K), LED2103.HS, U2103.9 (HPLED)
USD-1V8: C2105.1, L2101.1, L2102.2, LED2102.A, U2103.1 (SETT), U2103.2 (SETF), U2103.5 (SETI), U2103.14 (VDD)
USD-3V3: C2101.1, C2102.1, P2101.15, U2101.1 (VDD), U2102.5 (VDD)
USD-EN: P2101.9, U2103.15 (EN)
USD-I2C2-SCL: P2101.5, U2103.3 (SCL)
USD-I2C2-SDA: P2101.3, U2103.4 (SDA)
USD-INT: P2101.11, U2103.11 (!INT)
USD-STR: P2101.7, U2103.16 (STR)
USD-VBATT: L2101.2, P2101.18

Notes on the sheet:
µSD Breakout Board
(c) 2014 Golden Delicious Computers GmbH&Co. KG. Licensed under CC-BY-SA.
FX6-20S-0.8SV
ESD on CPU side
(1.5V - 3.6V)
Battery Cover detect
Camera Cover detect
pullup? or through GPIO?
Flash/Torch
V2b
or here?

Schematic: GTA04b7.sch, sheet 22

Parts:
G2201, G2202, G2204, G2205, G2207, G2209: SHIELDN900; N900-SPRING-A
G2203, G2206, G2208: SHIELDPAD-3.5X2.5; PAD-3.5X2.5
P2201, P2202: DF40C-60DP-0.4V

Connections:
GND3: G2201.1, G2202.1, G2203.1, G2204.1, G2205.1, G2206.1, G2207.1, G2208.1, G2209.1, P2201.2, P2201.29, P2201.32, P2201.59, P2202.2, P2202.29, P2202.32, P2202.59; also elsewhere on the board
VBATT_UPPER: P2201.1, P2201.30, P2201.31, P2201.60, P2202.1, P2202.31, P2202.60; also elsewhere on the board

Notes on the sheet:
B2B to lower board
(c) 2014 Golden Delicious Computers GmbH&Co. KG. Licensed under CC-BY-SA.
to be adjusted to lower board connector
SHIELD
V2b
